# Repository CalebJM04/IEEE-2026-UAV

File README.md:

This is a custom UAV PCB designed for competition at the 2026 IEEE Robotics and Automation Conference at UAH.

  *PCB Stackup

  This board was custom-designed by me. It features two linear regulators to power an RFM9x feather (which this PCB will support as the main microcontroller), a barometer for accurate altitude data,
and pinouts for ESC PWM support, as well as pinouts for a Pixy2 camera for image recognition.

  *PCB 3d view

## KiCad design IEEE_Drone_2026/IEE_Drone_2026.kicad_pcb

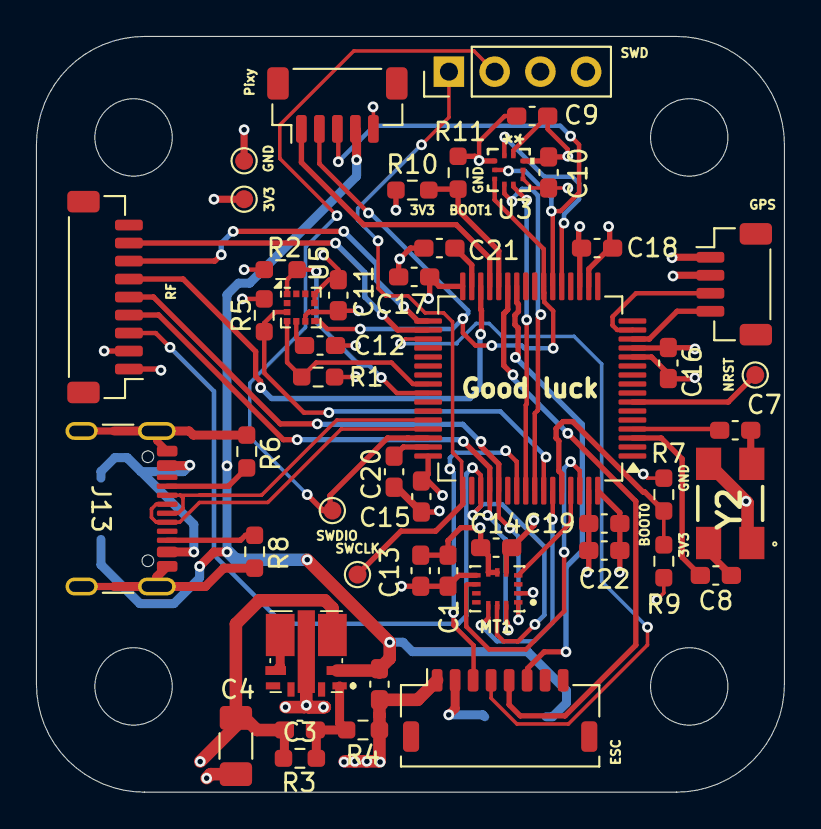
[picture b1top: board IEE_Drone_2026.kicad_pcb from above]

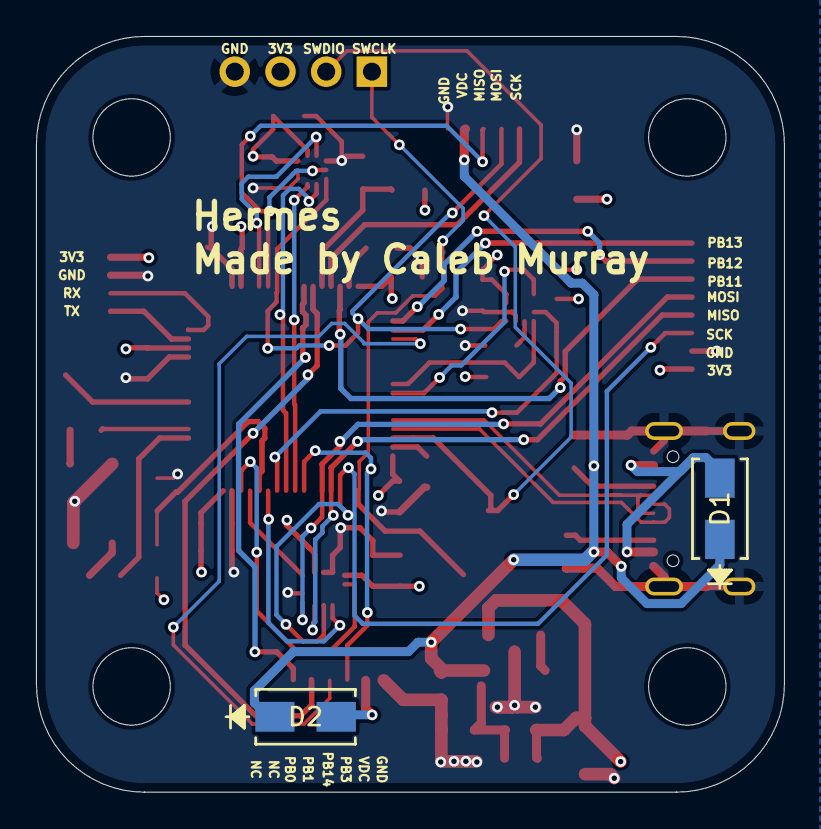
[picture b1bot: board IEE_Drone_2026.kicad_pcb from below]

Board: 4 copper layers, 41.6 x 42.0 mm, 54 parts (3 on the bottom side), 47 nets.

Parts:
3V3: TestPoint; TestPoint_Pad_D1.0mm
C1: 0.1uF; C_0603_1608Metric_Pad1.08x0.95mm_HandSolder
C2: 10uF; C_0603_1608Metric_Pad1.08x0.95mm_HandSolder
C3: 330pF; C_0603_1608Metric_Pad1.08x0.95mm_HandSolder
C4: 47uF; C_1206_3216Metric_Pad1.33x1.80mm_HandSolder
C7, C8: 12pF; C_0603_1608Metric_Pad1.08x0.95mm_HandSolder
C9, C10, C11, C15, C16, C17, C18, C22: 100nF; C_0603_1608Metric_Pad1.08x0.95mm_HandSolder
C12: 220nF; C_0603_1608Metric_Pad1.08x0.95mm_HandSolder
C13, C20, C21: 2.2uF; C_0603_1608Metric_Pad1.08x0.95mm_HandSolder
C14: 10nF; C_0603_1608Metric_Pad1.08x0.95mm_HandSolder
C19: 4.7uF; C_0603_1608Metric_Pad1.08x0.95mm_HandSolder
D1, D2: D_Schottky; DIODE_DO214AC
ESC: ESC; JST_SHL_SM08B-SHLS-TF_1x08-1MP_P1.00mm_Horizontal
GND: TestPoint; TestPoint_Pad_D1.0mm
GPS: GPS; JST_SH_BM04B-SRSS-TB_1x04-1MP_P1.00mm_Vertical
IC1: TPSM84209RKHT
J2, J3, J4, J5: M4 Mounting; MountingHole_4.3mm_M4
J13: USB_C_Receptacle_USB2.0_16P; USB_C_Receptacle_GCT_USB4105-xx-A_16P_TopMnt_Horizontal
MT1: ICM-42605; XDCR_ICM-42605
NRST: TestPoint; TestPoint_Pad_D1.0mm
Pixy: Pixy2; JST_SH_BM05B-SRSS-TB_1x05-1MP_P1.00mm_Vertical
R1, R2, R3, R5, R7, R9, R10, R11: 10k; R_0603_1608Metric_Pad0.98x0.95mm_HandSolder
R4: 2.2k; R_0603_1608Metric_Pad0.98x0.95mm_HandSolder
R6, R8: 5.1k; R_0603_1608Metric_Pad0.98x0.95mm_HandSolder
RF: RF; JST_SH_BM09B-SRSS-TB_1x09-1MP_P1.00mm_Vertical
SWCLK: TestPoint; TestPoint_Pad_D1.0mm
SWD: Conn_01x04_Socket; PinHeader_1x04_P2.54mm_Vertical
SWDIO: TestPoint; TestPoint_Pad_D1.0mm
U2: STM32F405RGTx; LQFP-64_10x10mm_P0.5mm
U3: BMP390; 10LGA_2X2X0p75_BOS
U5: LIS2MDL; LGA-12_2x2mm_P0.5mm
Y2: ABMM2-32.768MHZ-E2F-T; ABMM2

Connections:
+3.3V: 3V3.1, C1.1, C3.1, C4.1, C9.1, C10.1, C11.2, C13.1, C14.2, C15.1, C16.1, C17.1, C18.1, C19.1, C22.1, GPS.1, IC1.3 (VOUT), MT1.5 (VDDIO), MT1.8 (VDD), R1.1, R2.2, R3.1, R5.1, R9.1, R10.1, RF.1, SWD.3, U2.13 (VDDA), U2.19 (VDD), U2.32 (VDD), U2.48 (VDD), U2.64 (VDD), U3.1 (VDDIO), U3.10 (VDD), U5.9 (Vdd), U5.10 (Vdd_IO)
+VDC: C2.2, D1.1 (K), D2.1 (K), IC1.2 (VIN), Pixy.4
/BOOT0: R7.1, R9.2, U2.60 (BOOT0)
/D+: J13.A6 (D+), J13.B6 (D+), U2.45 (PA12)
/D-: J13.A7 (D-), J13.B7 (D-), U2.44 (PA11)
/MISO: Pixy.3, U2.22 (PA6), U3.4 (SDI)
/MISO (SPI3): MT1.14 (AP_SDA/AP_SDIO/AP_SDI), RF.4, U2.52 (PC11)
/MOSI: Pixy.2, U2.23 (PA7), U3.5 (SDO), U5.7 (DRDY)
/MOSI (SPI3): MT1.1 (AP_SDO/AP_AD0), RF.5, U2.53 (PC12)
/PB0: ESC.6, U2.26 (PB0)
/PB1: ESC.5, U2.27 (PB1)
/PB2: R10.2, R11.1, U2.28 (PB2)
/PB3: ESC.3, U2.55 (PB3)
/PB4: U2.56 (PB4), U3.7 (INT)
/PB5: U2.57 (PB5), U3.6 (CSB)
/PB6: R5.2, U2.58 (PB6), U5.3 (~CS)
/PB7: MT1.12 (AP_CS), U2.59 (PB7)
/PB8: MT1.4 (INT1/INT), U2.61 (PB8)
/PB9: MT1.9 (INT2/FSYNC), U2.62 (PB9)
/PB11: RF.6, U2.30 (PB11)
/PB12: RF.7, U2.33 (PB12)
/PB13: RF.8, U2.34 (PB13)
/PB14: ESC.4, U2.35 (PB14)
/Pin 2: D2.2 (A), ESC.2
/RX: GPS.3, U2.15 (PA1)
/SCK: Pixy.1, U2.29 (PB10)
/SCK (SPI3): MT1.13 (AP_SCL/AP_SCLK), RF.3, U2.51 (PC10)
/SCK(SPI1): U2.21 (PA5), U3.2 (SCK)
/SCL (I2C3): R2.1, U2.41 (PA8), U5.1 (SCL/SPC)
/SDA (I2C3): R1.2, U2.40 (PC9), U5.4 (SDA/SDI/SDO)
/SWCLK: SWCLK.1, SWD.1, U2.49 (PA14)
/SWDIO: SWD.2, SWDIO.1, U2.46 (PA13)
/TX: GPS.4, U2.14 (PA0)
GND: C1.2, C2.1, C4.2, C9.2, C10.2, C11.1, C12.1, C13.2, C14.1, C15.2, C16.2, C17.2, C18.2, C19.2, C20.2, C21.2, C22.2, ESC.1, GND.1, GPS.2, IC1.8 (GND), J13.A1 (GND), J13.A12 (GND), J13.B1 (GND), J13.B12 (GND), J13.S1 (SHIELD), MT1.2 (RESV), MT1.6 (GND), MT1.7 (RESV__2), Pixy.5, R4.2, R6.1, R7.2, R8.1, R11.2, RF.2, SWD.4, U2.12 (VSSA), U2.18 (VSS), U2.63 (VSS), U3.3 (VSS), U3.8 (VSS), U3.9 (VSS), U5.6 (GND), U5.8 (GND), Y2.1 (X1), Y2.3 (X2)
unnamed: D1.2 (A), J13.A4 (VBUS), J13.A9 (VBUS), J13.B4 (VBUS), J13.B9 (VBUS)
unnamed: C3.2, IC1.1 (FB), R3.2, R4.1
unnamed: IC1.4 (SW_1), IC1.5 (SW_2)
unnamed: J13.A5 (CC1), R6.2
unnamed: J13.B5 (CC2), R8.2
unnamed: NRST.1, U2.7 (NRST)
unnamed: C8.2, U2.3 (PC14)
unnamed: C7.2, U2.4 (PC15)
unnamed: C21.1, U2.31 (VCAP_1)
unnamed: C20.1, U2.47 (VCAP_2)
unnamed: C12.2, U5.5 (C1)
unnamed: C7.1, Y2.2 (GND_1)
unnamed: C8.1, Y2.4 (GND_2)

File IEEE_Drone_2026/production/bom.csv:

Designator,Footprint,Quantity,Value,LCSC Part #
"3V3, GND, NRST, SWCLK, SWDIO",TestPoint_Pad_D1.0mm,5,TestPoint,
C1,0603,1,0.1uF,
"C10, C11, C15, C16, C17, C18, C22, C9",0603,8,100nF,
C12,0603,1,220nF,
"C13, C20, C21",0603,3,2.2uF,
C14,0603,1,10nF,
C19,0603,1,4.7uF,
C2,0603,1,10uF,
C3,0603,1,330pF,
C4,1206,1,47uF,
"C7, C8",0603,2,12pF,
IC1,TPSM84209RKHT,1,TPSM84209RKHT,
J13,USB_C_Receptacle_GCT_USB4105-xx-A_16P_TopMnt_Horizontal,1,USB_C_Receptacle_USB2.0_16P,
MT1,XDCR_ICM-42605,1,ICM-42605,
"R1, R10, R11, R2, R3, R5, R7, R9",0603,8,10k,
R4,0603,1,2.2k,
"R6, R8",0603,2,5.1k,
RF,JST_SH_BM09B-SRSS-TB_1x09-1MP_P1.00mm_Vertical,1,RF,
SWD,PinHeader_1x04_P2.54mm_Vertical,1,Conn_01x04_Socket,
U2,LQFP-64_10x10mm_P0.5mm,1,STM32F405RGTx,
U3,10LGA_2X2X0p75_BOS,1,BMP390,
U5,LGA-12_2x2mm_P0.5mm,1,LIS2MDL,
Y2,ABMM2,1,ABMM2-32.768MHZ-E2F-T,

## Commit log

2025-08-31 First push (test1.txt)
    Test commit w/ github desktop
2025-08-31 first drone v commit
2025-08-31 redesign of feather system to incorporate ESC system
    added mounting pins, changed board size, redesigned pwr system and moved it and barometer, removed individual servo pins and added 1x6 conn for ESC
2025-08-31 added second power regulator for 6v to pixy2m added a couple more labels
2025-08-31 changed some slight routing and added text
2025-09-02 imrpoved routing
2025-09-02 updated ESC connector to fix conn issue.
    will need to twist the ESC connection cable to properly connect to the ESC
2025-09-02 improve one via line
2025-09-02 connected unconnected track in 6v pwr IC
2025-09-02 added a gnd pour on top...? not sure if best path or not
2025-09-02 added crappy mounting holes. probably need to redo
2025-09-03 added my name
2025-09-03 first production push
2025-09-04 removed solder mask over battery pours
2025-09-09 designed transistor circuit & pcb
2025-09-09 added easter egg...
2025-09-10 added D11 title
2025-09-10 removed silkscreen text under pwr IC
2025-09-10 made production
2025-09-10 updated silkscreen text
2025-09-11 updated c4 c5 c7 to 1206
    coudn't find 0603 in spec
2025-09-11 updated routing for 1206 caps
2025-09-11 cleaned up routing and merlin image
2025-09-11 fixed DRC problems, 0 errors
    keepout errors from the fill to remove gnd
2025-09-11 make prod for order
2025-09-11 fixes
2025-09-16 added a switch for VDC
2025-09-17 updated text pos
2025-09-17 make prod, ordered PCB
2025-09-29 add 3d file (no comps)
2025-09-29 create the stl
2025-09-29 added all the order confirmations
2025-10-13 init code folder
2025-10-19 try to fix mounting holes
2025-10-19 update sch last time before redesign
2025-10-20 added new schematic items
2025-10-20 added zoe
2025-10-20 added new gps:m10q
2025-10-20 slight labeling updates
2025-10-25 removed bmp280 and added 390
2025-10-25 added bmp390 and wired it for 4 wire spi
    miso = 4
    mosi = 5
    int = PB4
    CSB = pb5
    SCK = sck(pb10)
2025-10-25 added sam10mq to new rev
2025-10-25 added wiring for lis2mdl
2025-10-25 wired the imu
2025-10-27 start pcb
2025-10-29 made power module and removed switch
    we don't need a switch. we can just say we will unplug the battery, and if we need a "SWITCH" we will just solder a physical one or sm
2025-10-29 updated connector and moved voltage reg
2025-10-29 further design
2025-10-29 general wiring & fixes
    fixed VDD and VDDIO being grounded... not tied to 3v3dc
2025-10-29 fixed more wiring
2025-10-29 added pwr on MCU cap bus
2025-10-30 some routing updates
2025-10-30 slight routing update
2025-10-30 routed more things
2025-10-30 removed transistor cirucit !!!
2025-10-30 new dimensions for board
2025-10-30 completely updated design
2025-10-31 updated lots
    finished board internals routing, starting schematic routing for the gps, rf, and pixy
2025-10-31 finished schematic connections for pins
2025-10-31 added gnd planes on top and bottom layer
    DRC is passing with no errors now
2025-10-31 made prod
2025-10-31 slight routing updates
2025-11-03 complete redesign
2025-11-03 updated silkscreen
2025-11-03 added chamfered edges
2025-11-03 fixed drc clearance violations
2025-11-03 added bottom layer gnd plane
2025-11-03 silkscreen updates
2025-11-03 silkscreen text updates
2025-11-03 added SWD testpoints
2025-11-03 updated board dimensions to fit the ESC
    tested hole fit and it worked
2025-11-03 slight routing
    see if i can maybe swap pixy and rf to make sure the hole isn't blocked?
2025-11-03 final rev of routing with the trad routing
    next revs will be with smoothed
2025-11-03 back to straight routing..
2025-11-03 updated 3v3 routing for buck
2025-11-03 improved usb routing
2025-11-03 fixed the fill
2025-11-03 fixed 3v3 routing for bmp390
2025-11-03 added optional boot pull ups
    Obv only 1 is to be used at a time. If boot is pulled LOW, it boots from flash. If boot is pulled HIGH, the boot state depends on pin BOOT1 (PB2)
2025-11-03 added pull resistors for BOOT1 (PB2)
    and rerouted the ESC PB2 connection to PB14
2025-11-03 added text to the BOOT0 and BOOT1 pull resistors
2025-11-03 made new prod (latest)
2025-11-05 cleaned drc pass and made prod
2025-11-05 active
2025-11-09 prod. ordering!
2025-11-09 added BOM
2025-11-11 d+ & d- routing fix
2025-11-11 made latest prod w/ new usb
2025-11-21 added diodes. they are on the bottom
    I don't like them on the bottom of the board but idk if I can even change them ngl
2025-11-21 made prod with new diodes
2026-01-04 ordered w/ diode
2026-01-05 ordered new rev
